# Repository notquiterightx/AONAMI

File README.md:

<picture align="center">
  <source media="(prefers-color-scheme: dark)" srcset="docs/images/IMG_8813.jpeg">
  <source media="(prefers-color-scheme: light)" srcset="docs/images/IMG_8813.jpeg">
  
</picture>

<h1 align="left">AŌNAMI</h1>

A wireless ergonomic split keyboard featuring 40 keys and 2 encoders. Designed around the Seeed Studio XIAO nRF52840

## Features

- Fully open sourced hardware & firmware
- Reversible PCB
- Two possible formats
    - Low Profile with a 200mAh battery
    - Tentable with a 600mAh battery
- Choc v1/v2 hot swappable switches
- Choc spacing
- ZMK firmware for remapping keys
- Fully wireless or wired through USB-C

## Build Guide
The build guide is still a WIP but you can access the BOM here: [Build guide](docs/buildguide.md)

## PCB

You can check the source Ergogen files used to design this keyboard [here](/ergogen/). If you want the ready-to-order gerber files you can check them out [here](/pcbs/).

## Firmware

- [ZMK Precompiled](/firmware/). This is still a work in progress, there are a lot of tailor-made combos for myself and some extra layers that may not be as useful to you. If you want to adjust it to your needs check out the ZMK Source.
- [ZMK Source](https://github.com/notquiterightx/zmk-config-aonami)

## Case

### Tenting

The Maker World case project can be found [here](https://makerworld.com/en/models/3670155-aonami-keyboard-tenting-case#profileId-4213444). Alternatively, you can access the STEP or 3MF files [here](/case/tenting/).

### Low Profile
[The case for the low-profile format is still a WIP]

## Gallery
### Tenting Build

\
\
\
\

### Low Profile Build
[The low profile build is still ongoing]

***

## Inspiration
The design of this keyboard wouldn't have been possible without many open source projects that I've learned a lot from. Here are some of the ones that made the most impact:
- [TOTEM by GEIST](https://github.com/GEIGEIGEIST/TOTEM) (and all of his keyboards for that matter)
- [Pica40 by zzeneg](https://github.com/zzeneg/pica40)
- [Flake by Lever Tech](https://github.com/lever-tech/flake)
- [Cornix LP by JezailFunder](https://jezailfunder.com/products/cornix-lp-keyboard)

***
If you end up building this keyboard, don't hesitate to reach out to me and give me any feedback or pictures you may have. This project has taken some time and I'd love to see if you end up using it.

If you want to support this project or any other ones I may make in the future, you can [leave me a tip](https://ko-fi.com/notquiteright), but this is still by all means an open source project and you shouln't feel any pressure to do so.

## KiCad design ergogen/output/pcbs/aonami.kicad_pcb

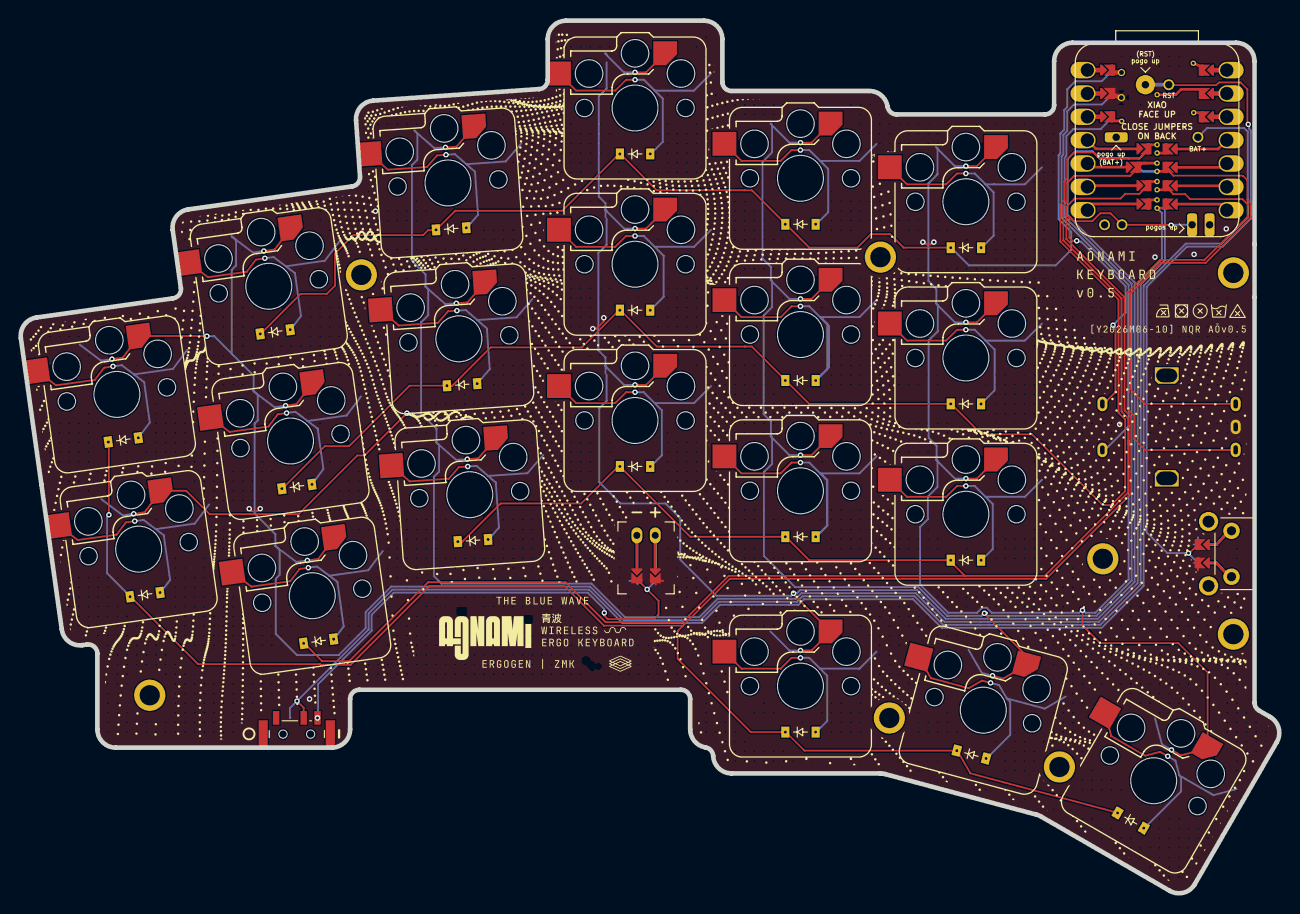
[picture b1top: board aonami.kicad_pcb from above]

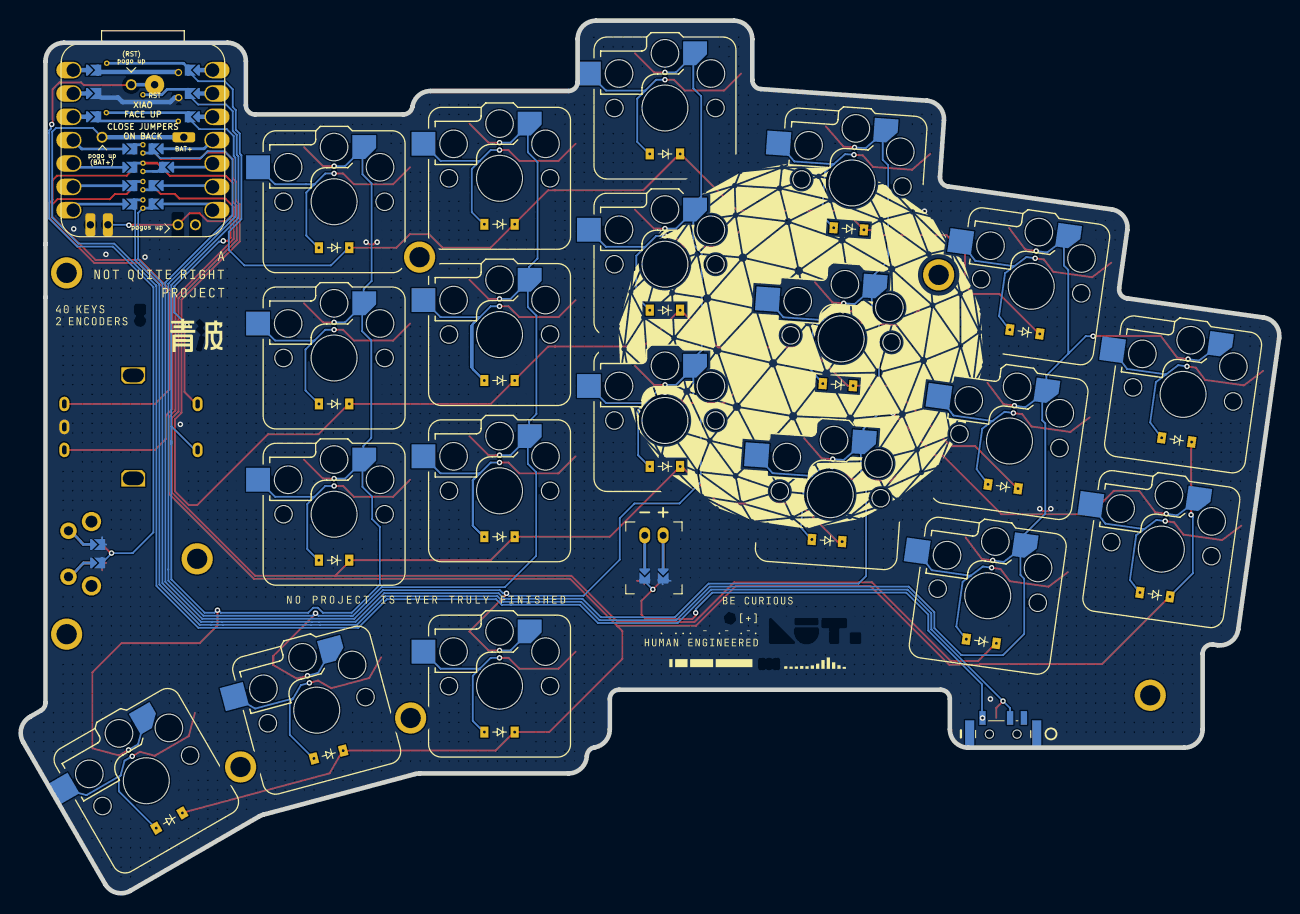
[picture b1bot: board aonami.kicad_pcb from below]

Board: 2 copper layers, 136.9 x 94.9 mm, 51 parts (21 on the bottom side), 31 nets.

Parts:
D1, D2, D3, D4, D5, D6, D7, D8, D9, D10, D11, D12, D13, D14, D15, D16, D17, D18, D19, D20: diode_tht_sod123
H1, H2, H2#2, H2#3, H3, H3#2, H4, H5: mounting_hole_plated
JST1: battery_connector_jst_ph_2
PWR1: power_switch_smd_side
RE1: rotary_encoder_ec11_ec12
S1, S2, S3, S4, S5, S6, S7, S8, S9, S10, S11, S12, S13, S14, S15, S16, S17, S18, S19, S20: switch_choc_v1_v2

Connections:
BAT_C: JST1.1, PWR1.3
GND: JST1.2, RE1.B
col_index: S12.1, S13.1, S14.1, S19.1
col_inner: RE1.S1, S15.1, S16.1, S17.1, S20.1
col_middle: S9.1, S10.1, S11.1, S18.1
col_pinky: S2.1, S3.1, S4.1, S5.1
col_ring: S1.1, S6.1, S7.1, S8.1
extra_home: D1.2, S1.2
extra_top: D2.2, S2.2
far_thumb-cluster: D20.2, S20.2
index_bottom: D12.2, S12.2
index_home: D13.2, S13.2
index_top: D14.2, S14.2
inner_bottom: D15.2, S15.2
inner_home: D16.2, S16.2
inner_top: D17.2, S17.2
mid_thumb-cluster: D19.2, S19.2
middle_bottom: D9.2, S9.2
middle_home: D10.2, S10.2
middle_top: D11.2, S11.2
near_thumb-cluster: D18.2, S18.2
pinky_bottom: D3.2, S3.2
pinky_home: D4.2, S4.2
pinky_top: D5.2, S5.2
ring_bottom: D6.2, S6.2
ring_home: D7.2, S7.2
ring_top: D8.2, S8.2
row_bottom: D3.1, D6.1, D9.1, D12.1, D15.1
row_home: D4.1, D7.1, D10.1, D13.1, D16.1
row_thumb: D1.1, D2.1, D18.1, D19.1, D20.1
row_top: D5.1, D8.1, D11.1, D14.1, D17.1
